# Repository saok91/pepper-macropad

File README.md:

# pepper – Custom Macropad PCB

This repository contains the **source design files** for **pepper**, a custom mechanical macropad designed using **KiCad**.

## Repository Contents

### Source files (tracked)
These files are the **source of truth** for the design and are version-controlled:

- `pepper.kicad_sch` – Schematic
- `pepper.kicad_pcb` – PCB layout
- `pepper.kicad_pro` – KiCad project configuration

### Generated files (ignored)
The following files are intentionally **not tracked** via `.gitignore`:

- 3D exports: `*.stl`, `*.step`, `*.stp`, `*.wrl`, `*.obj`
- Fabrication outputs: Gerbers, drills, pick-and-place files
- KiCad autosave, backup, and cache files
- BOM exports (`.csv`, `.xlsx`)
- OS / editor temporary files

Generated outputs may be shared separately (e.g. releases) when the design is ready.

## Tools

- **EDA**: KiCad (v7+ recommended)
- **Version control**: Git

## Project Status

- Work in progress (WIP)
- Not yet released for manufacturing

## Notes

- This repository contains **design sources only**
- Do not manufacture or modify outputs without validating against the KiCad source files

## License

TBD

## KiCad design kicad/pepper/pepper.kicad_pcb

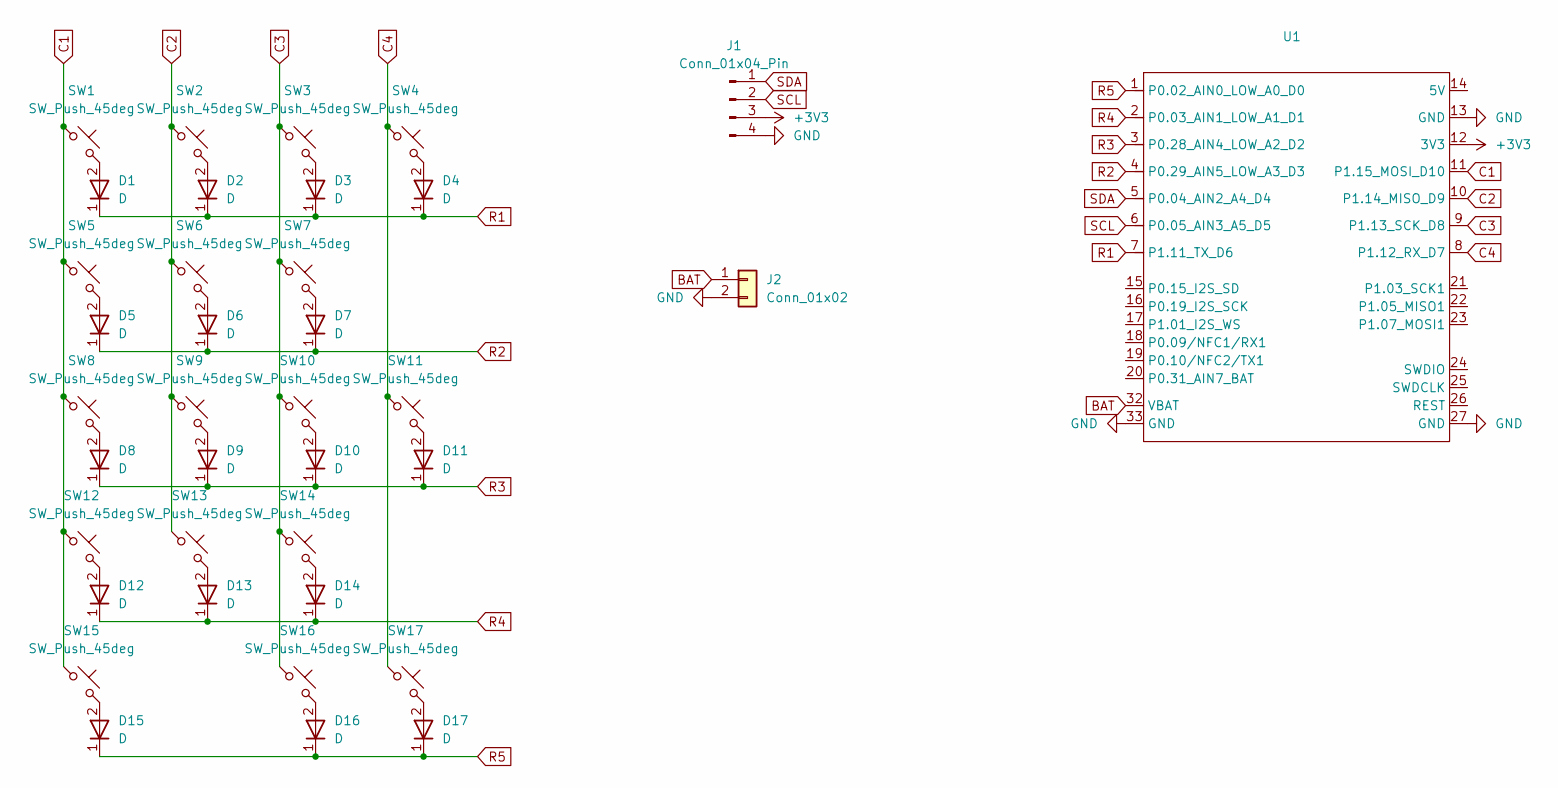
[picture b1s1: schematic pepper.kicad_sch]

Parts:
D1, D2, D3, D4, D5, D6, D7, D8, D9, D10, D11, D12, D13, D14, D15, D16, D17: D; D_SOD-123
J1: Conn_01x04_Pin; SSD1306
J2: Conn_01x02; JST_XH_S2B-XH-A_1x02_P2.50mm_Horizontal
SW1, SW2, SW3, SW4, SW5, SW6, SW7, SW8, SW9, SW10, SW12, SW13, SW14, SW16: SW_Push_45deg; MNP_SW_Hotswap_Kailh_MX_1.00u
SW11, SW17: SW_Push_45deg; MNP_SW_Hotswap_Kailh_MX_2.00u_90deg
SW15: SW_Push_45deg; MNP_SW_Hotswap_Kailh_MX_2.00u
U1: XIAO-nRF52840-Plus-SMD

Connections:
+3V3: J1.3, U1.12 (3V3)
BAT: J2.1, U1.32 (VBAT)
C1: SW1.1, SW5.1, SW8.1, SW12.1, SW15.1, U1.11 (P1.15_MOSI_D10)
C2: SW2.1, SW6.1, SW9.1, SW13.1, U1.10 (P1.14_MISO_D9)
C3: SW3.1, SW7.1, SW10.1, SW14.1, SW16.1, U1.9 (P1.13_SCK_D8)
C4: SW4.1, SW11.1, SW17.1, U1.8 (P1.12_RX_D7)
GND: J1.4, J2.2, U1.13 (GND), U1.27 (GND), U1.33 (GND)
unnamed: D1.2 (A), SW1.2
unnamed: D2.2 (A), SW2.2
unnamed: D3.2 (A), SW3.2
unnamed: D4.2 (A), SW4.2
unnamed: D5.2 (A), SW5.2
unnamed: D6.2 (A), SW6.2
unnamed: D7.2 (A), SW7.2
unnamed: D8.2 (A), SW8.2
unnamed: D9.2 (A), SW9.2
unnamed: D10.2 (A), SW10.2
unnamed: D11.2 (A), SW11.2
unnamed: D12.2 (A), SW12.2
unnamed: D13.2 (A), SW13.2
unnamed: D14.2 (A), SW14.2
unnamed: D15.2 (A), SW15.2
unnamed: D16.2 (A), SW16.2
unnamed: D17.2 (A), SW17.2
R1: D1.1 (K), D2.1 (K), D3.1 (K), D4.1 (K), U1.7 (P1.11_TX_D6)
R2: D5.1 (K), D6.1 (K), D7.1 (K), U1.4 (P0.29_AIN5_LOW_A3_D3)
R3: D8.1 (K), D9.1 (K), D10.1 (K), D11.1 (K), U1.3 (P0.28_AIN4_LOW_A2_D2)
R4: D12.1 (K), D13.1 (K), D14.1 (K), U1.2 (P0.03_AIN1_LOW_A1_D1)
R5: D15.1 (K), D16.1 (K), D17.1 (K), U1.1 (P0.02_AIN0_LOW_A0_D0)
SCL: J1.2, U1.6 (P0.05_AIN3_A5_D5)
SDA: J1.1, U1.5 (P0.04_AIN2_A4_D4)

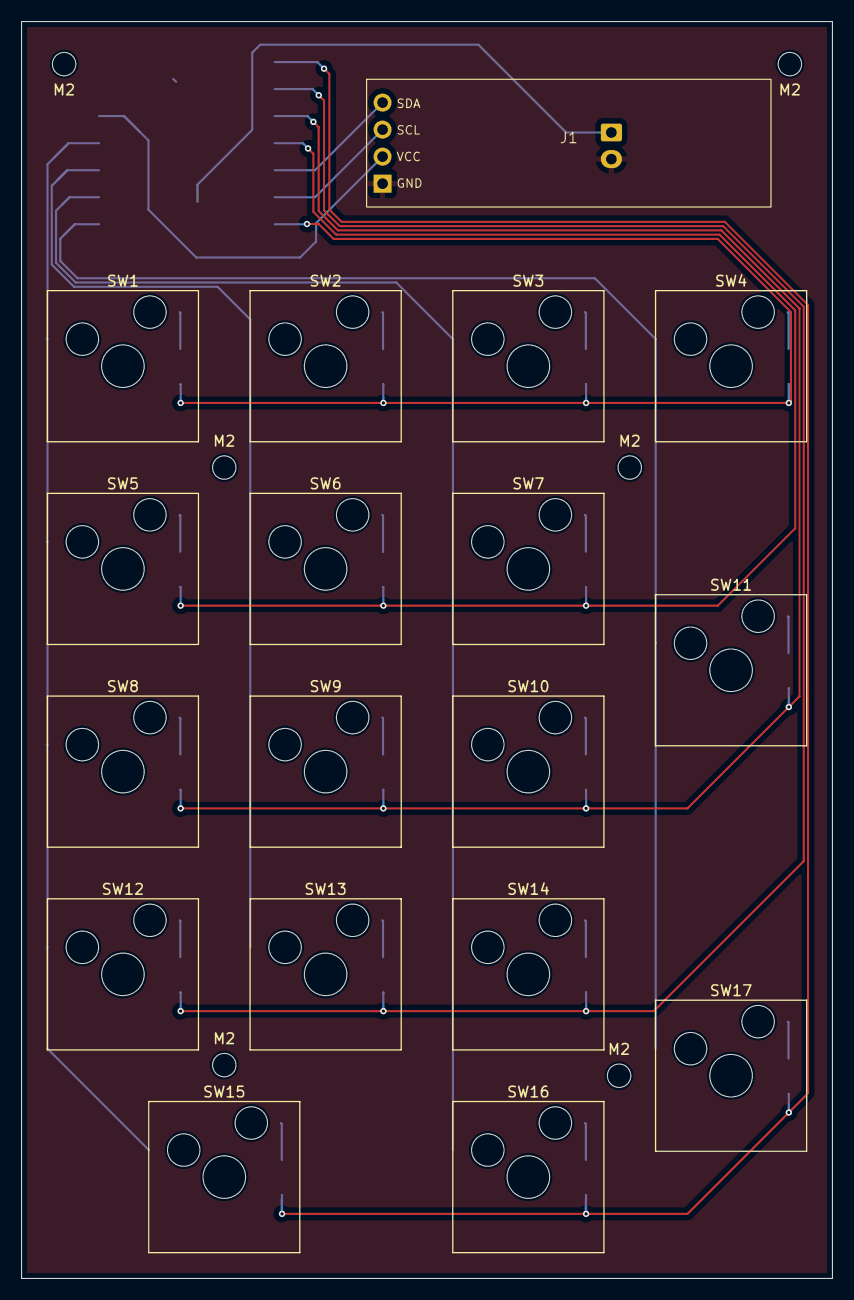
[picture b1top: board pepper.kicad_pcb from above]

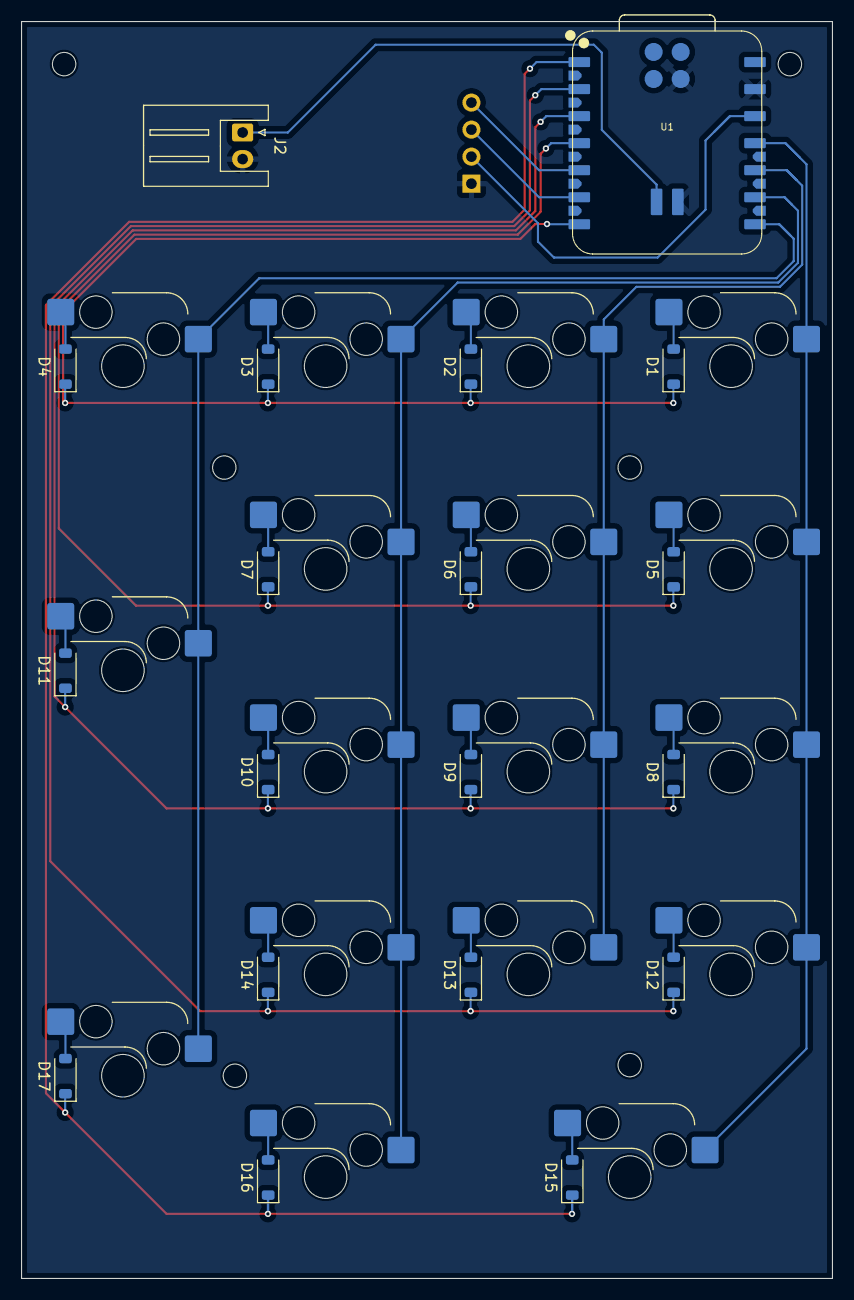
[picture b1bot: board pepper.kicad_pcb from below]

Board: 2 copper layers, 76.2 x 118.1 mm, 43 parts (19 on the bottom side), 31 nets.

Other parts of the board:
M2, M2#2, M2#3, M2#4, M2#5, M2#6: MountingHole_2.2mm_M2

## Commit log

2026-02-01 init commit
2026-02-01 fix: gitignore updated
2026-02-01 fix: readme edit
